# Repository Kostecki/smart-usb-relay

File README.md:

# Smart USB Relay

An inline USB-C box that switches and meters 5 V power to a USB gadget (lamp, fan, sensor) from Home Assistant. Charger → box → device.

- ESP32-H2 SuperMini running ESPHome over Thread (OTA, no Wi-Fi)
- TPS2557 current-limited switch (3 A), INA226 voltage/current/power metering → kWh in the Energy dashboard
- USB-C in and out: fixed 5 V sink towards the charger, 1.5 A / 3 A source towards the device (follows what the charger offers)
- 60 × 30 mm, 2 layers, assembled by JLCPCB (except the SuperMini, which sits on headers)

The full design, every decision behind it, and the pre-order checklist are in [SPEC.md](SPEC.md).

## Layout

| Path | What |
|---|---|
| `hardware/` | KiCad 10 project, project symbol/footprint libraries, footprints converted from LCSC (`lcsc/`) |
| `firmware/` | ESPHome configuration |
| `scripts/fab.sh` | ERC + DRC (with schematic parity), then Gerbers, drill, BOM and CPL for JLCPCB into `fab/` |

## Firmware

The config lives in the Home Assistant ESPHome dashboard (ESPHome 2026.10.0 or newer) and is edited there. `firmware/smart-usb-relay.yaml` is a copy, updated by hand when the behaviour changes.

1. In the dashboard's **Secrets**, add `thread_tlv` and `api_encryption_key` (`openssl rand -base64 32`; it also encrypts OTA). `firmware/secrets.example.yaml` explains how to get the Thread TLV with an Apple border router: send the credentials from the iPhone companion app, then read them with `thread/get_dataset_tlv` in the browser console.
2. Create a new device, skip the Wi-Fi questions, and replace its YAML with `firmware/smart-usb-relay.yaml`. For a second box, change `name` and `friendly_name` under `esphome:`.
3. Flash the SuperMini over its own USB-C **before** fitting it to the board: **Install → Plug into this computer** (Chrome or Edge). If the port doesn't show up, hold BOOT while plugging it in.
4. It joins your Thread network as a router and Home Assistant discovers it. Later updates: **Install → Wirelessly**.

Before it's on the board, the ADC pins float, so "Device attached" and the charger readings are meaningless.

Entities: Output, Device attached, Output powered, Overcurrent tripped, Voltage, Current, Power, Energy, Charger voltage, Charger advertised current, Advertised to device; config: Power-on behavior, Force output, Current limit.

## Order files

CI runs `scripts/fab.sh` on every change to the hardware and uploads `fab/` as a build artifact. Locally:

```sh
KICAD_CLI=/Applications/KiCad/KiCad.app/Contents/MacOS/kicad-cli scripts/fab.sh
```

Upload `fab/smart-usb-relay-gerbers.zip`, then the BOM and CPL for assembly. Leave U1 (SuperMini), the test pads and the mounting holes out of assembly (they're already excluded from the BOM and CPL), and choose "Remove Order Number".

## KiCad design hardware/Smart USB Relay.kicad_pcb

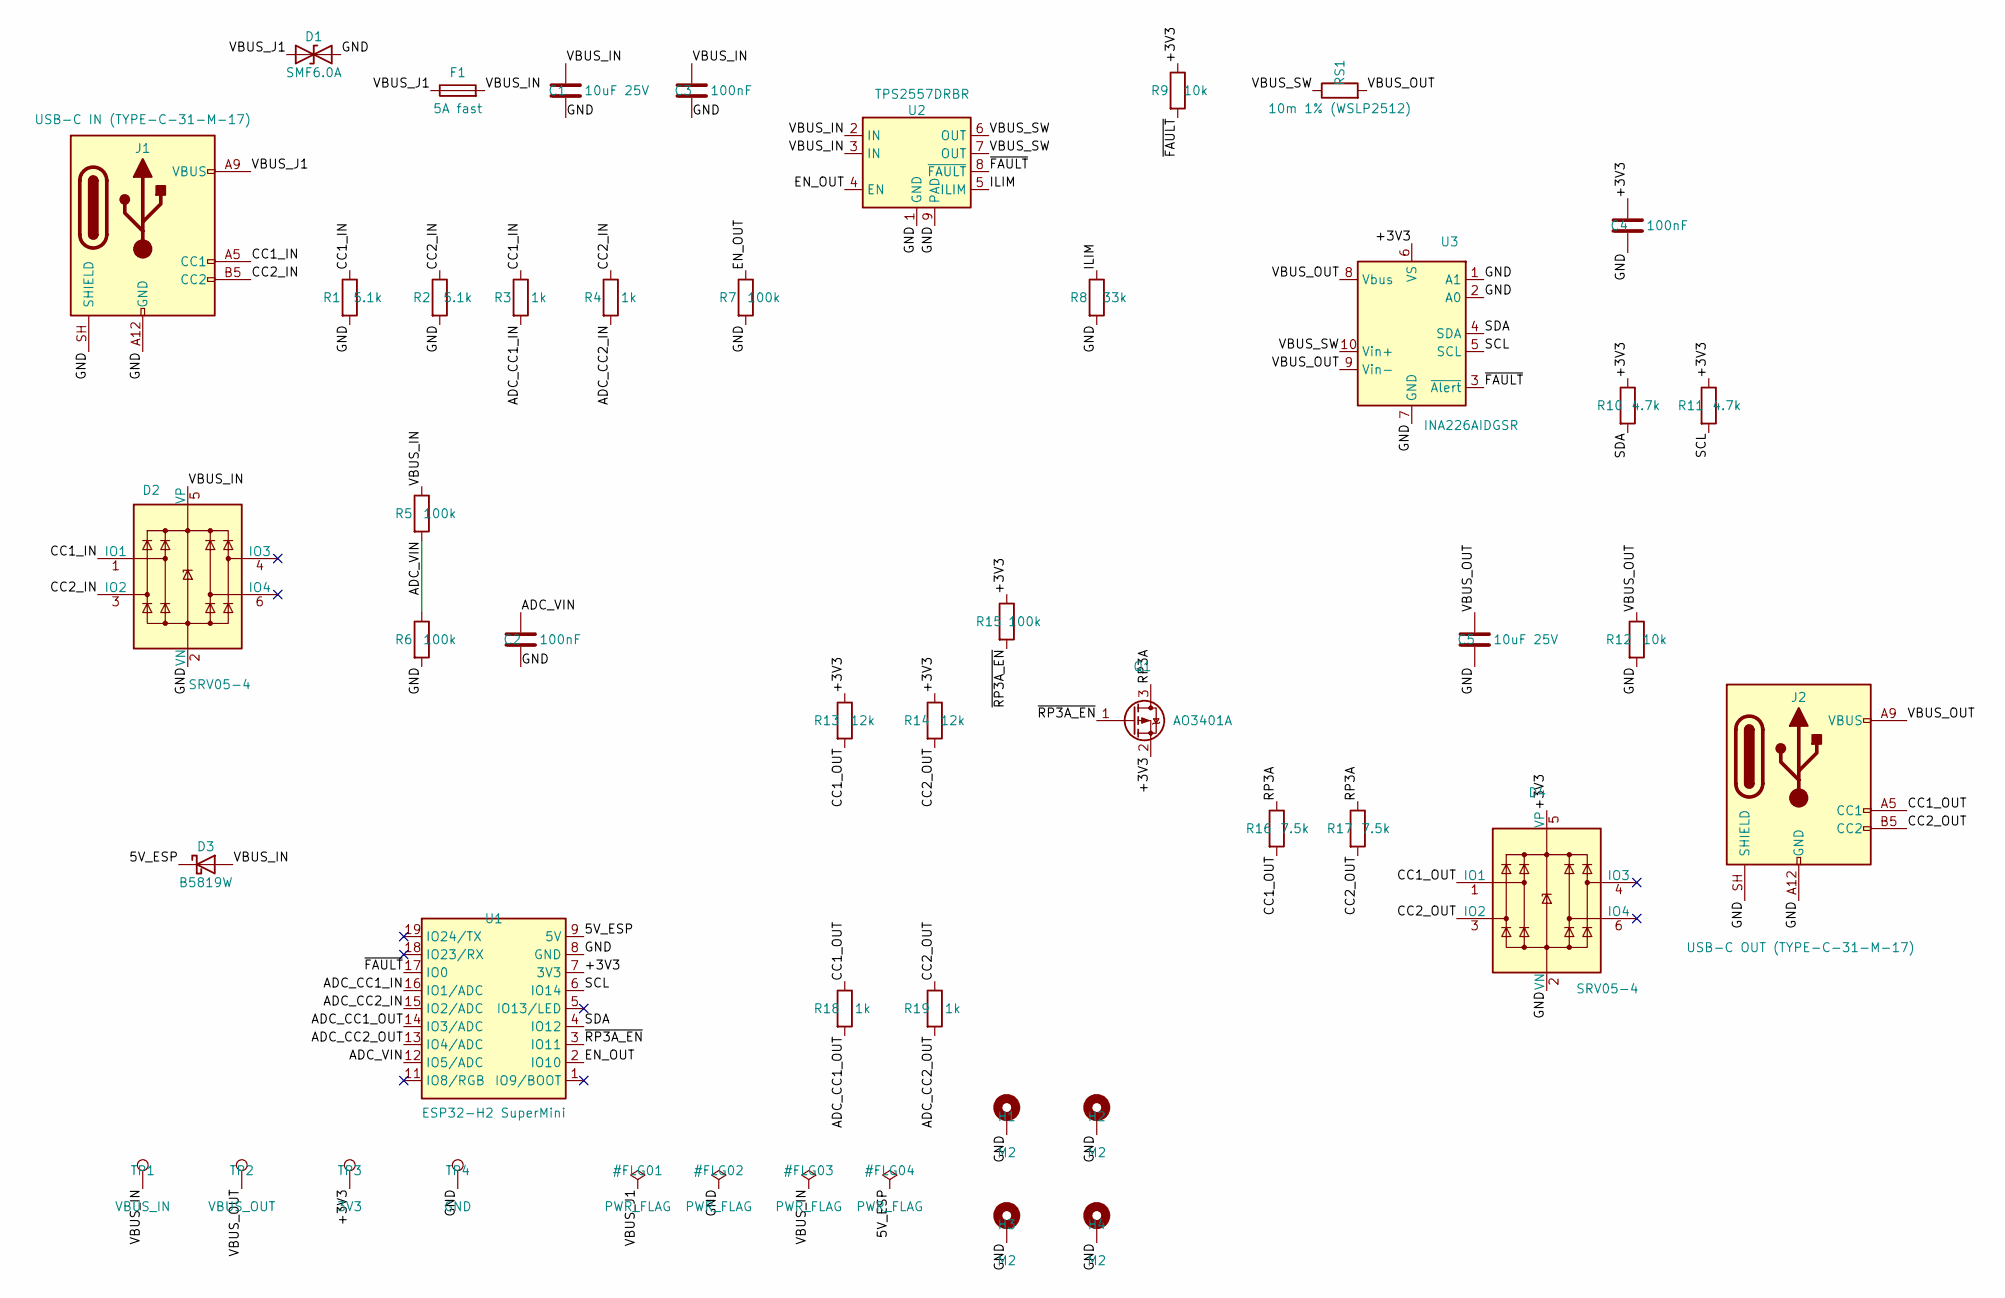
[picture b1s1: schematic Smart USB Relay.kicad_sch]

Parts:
C1, C5: 10uF 25V; C_0805_2012Metric; LCSC C15850
C2, C3, C4: 100nF; C_0603_1608Metric; LCSC C14663
D1: SMF6.0A; SOD-123FL_L2.7-W1.8-LS3.8-RD; LCSC C19077499
D2, D4: SRV05-4; SOT-23-6_L2.9-W1.6-P0.95-LS2.8-BR; LCSC C85364
D3: B5819W; SOD-123_L2.7-W1.6-LS3.7-RD-1; LCSC C8598
F1: 5A fast; F1206; LCSC C136351
H1, H2, H3, H4: M2; MountingHole_2.2mm_M2_Pad_Via
J1: USB-C IN (TYPE-C-31-M-17); USB_C_Receptacle_HRO_TYPE-C-31-M-17; LCSC C283540
J2: USB-C OUT (TYPE-C-31-M-17); USB_C_Receptacle_HRO_TYPE-C-31-M-17; LCSC C283540
Q1: AO3401A; SOT-23_L2.9-W1.3-P1.90-LS2.4-BR; LCSC C15127
R1, R2: 5.1k; R_0603_1608Metric; LCSC C23186
R3, R4, R18, R19: 1k; R_0603_1608Metric; LCSC C21190
R5, R6, R7, R15: 100k; R_0603_1608Metric; LCSC C25803
R8: 33k; R_0603_1608Metric; LCSC C4216
R9, R12: 10k; R_0603_1608Metric; LCSC C25804
R10, R11: 4.7k; R_0603_1608Metric; LCSC C23162
R13, R14: 12k; R_0603_1608Metric; LCSC C22790
R16, R17: 7.5k; R_0603_1608Metric; LCSC C23234
RS1: 10m 1% (WSLP2512); R2512; LCSC C241862
TP1: VBUS_IN; TestPoint_Pad_D1.5mm
TP2: VBUS_OUT; TestPoint_Pad_D1.5mm
TP3: 3V3; TestPoint_Pad_D1.5mm
TP4: GND; TestPoint_Pad_D1.5mm
U1: ESP32-H2 SuperMini; ESP32-H2_SuperMini_Header
U2: TPS2557DRBR; SON-8_L3.0-W3.0-P0.65-LS3.0-BL-EP; LCSC C130056
U3: INA226AIDGSR; MSOP-10_L3.0-W3.0-P0.50-LS5.0-BL; LCSC C49851

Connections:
/5V_ESP: D3.1 (K), U1.9 (5V)
/+3V3: C4.1, D4.5 (VP), Q1.2 (S), R9.1, R10.1, R11.1, R13.1, R14.1, R15.1, TP3.1, U1.7 (3V3), U3.6 (VS)
/ADC_CC1_IN: R3.2, U1.16 (IO1/ADC)
/ADC_CC1_OUT: R18.2, U1.14 (IO3/ADC)
/ADC_CC2_IN: R4.2, U1.15 (IO2/ADC)
/ADC_CC2_OUT: R19.2, U1.13 (IO4/ADC)
/ADC_VIN: C2.1, R5.2, R6.1, U1.12 (IO5/ADC)
/CC1_IN: D2.1 (IO1), J1.A5 (CC1), R1.1, R3.1
/CC1_OUT: D4.1 (IO1), J2.A5 (CC1), R13.2, R16.2, R18.1
/CC2_IN: D2.3 (IO2), J1.B5 (CC2), R2.1, R4.1
/CC2_OUT: D4.3 (IO2), J2.B5 (CC2), R14.2, R17.2, R19.1
/EN_OUT: R7.1, U1.2 (IO10), U2.4 (EN)
/GND: C1.2, C2.2, C3.2, C4.2, C5.2, D1.2 (A2), D2.2 (VN), D4.2 (VN), H1.1, H2.1, H3.1, H4.1, J1.A12 (GND), J1.B12 (GND), J1.SH (SHIELD), J2.A12 (GND), J2.B12 (GND), J2.SH (SHIELD), R1.2, R2.2, R6.2, R7.2, R8.2, R12.2, TP4.1, U1.8 (GND), U2.1 (GND), U2.9 (PAD), U3.1 (A1), U3.2 (A0), U3.7 (GND)
/ILIM: R8.1, U2.5 (ILIM)
/RP3A: Q1.3 (D), R16.1, R17.1
/SCL: R11.2, U1.6 (IO14), U3.5 (SCL)
/SDA: R10.2, U1.4 (IO12), U3.4 (SDA)
/VBUS_IN: C1.1, C3.1, D2.5 (VP), D3.2 (A), F1.2, R5.1, TP1.1, U2.2 (IN), U2.3 (IN)
/VBUS_J1: D1.1 (A1), F1.1, J1.A9 (VBUS), J1.B9 (VBUS)
/VBUS_OUT: C5.1, J2.A9 (VBUS), J2.B9 (VBUS), R12.1, RS1.2, TP2.1, U3.8 (Vbus), U3.9 (Vin-)
/VBUS_SW: RS1.1, U2.6 (OUT), U2.7 (OUT), U3.10 (Vin+)
/~FAULT: R9.2, U1.17 (IO0), U2.8 (~FAULT), U3.3 (~Alert)
/~RP3A_EN: Q1.1 (G), R15.2, U1.3 (IO11)

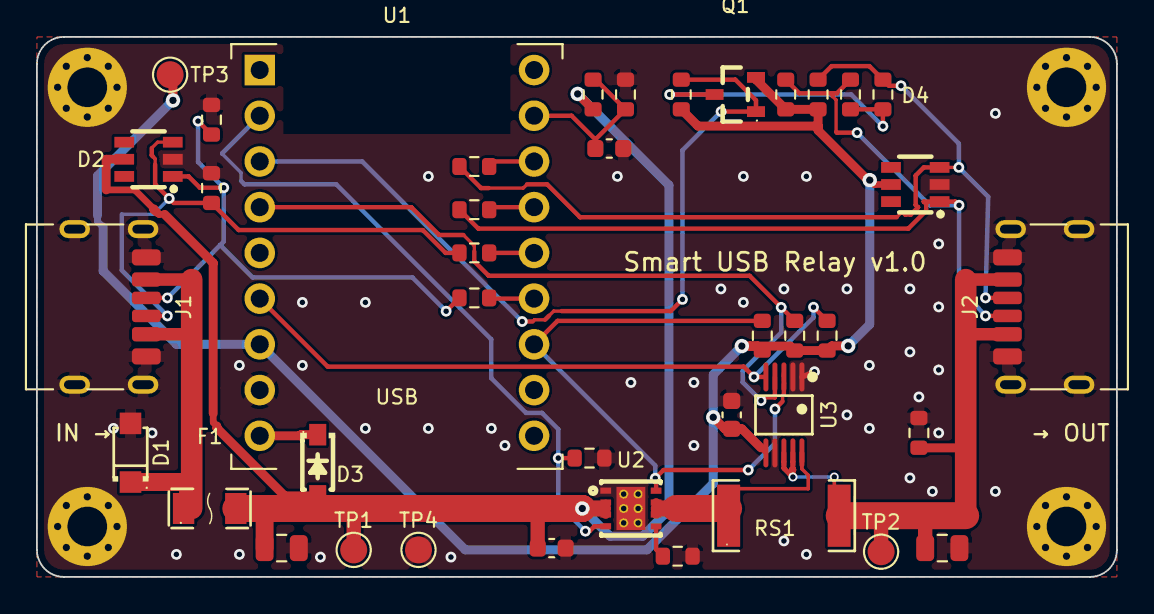
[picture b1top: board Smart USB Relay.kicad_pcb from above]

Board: 2 copper layers, 60.0 x 30.0 mm, 44 parts (0 on the bottom side), 23 nets.

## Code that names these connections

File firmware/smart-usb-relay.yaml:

# Board: Generic ESP32-H2 Board (Generic)
# Definition: definitions/boards/generic-esp32h2/manifest.yaml

# Smart USB Relay — ESP32-H2 SuperMini, ESPHome over Thread.
# Hardware, pin map and behaviour: ../SPEC.md
esphome:
  name: smart-usb-relay # unique per box
  friendly_name: Smart USB Relay
  min_version: 2026.10.0
  on_boot:
    # After the restored select/globals are loaded, apply the power-on behaviour.
    priority: -100
    then:
      - lambda: |-
          const auto option = id(power_on_behavior).current_option();
          if (option == "Off") {
            id(output_requested) = false;
          } else if (option == "On") {
            id(output_requested) = true;
          }
          // "Previous": keep the restored output_requested.

esp32:
  variant: esp32h2
  flash_size: 4MB # SuperMini: ESP32-H2 with 4 MB in-package flash
  framework:
    type: esp-idf

logger:
  level: INFO

network:
  enable_ipv6: true

openthread:
  device_type: FTD # mains powered, so a Thread router
  tlv: !secret thread_tlv
  force_dataset: true

api:
  encryption:
    key: !secret smart_usb_relay__api_encryption_key
ota:
  - platform: esphome
    encryption: {} # reuses the api encryption key

status_led:
  pin: GPIO13 # onboard blue LED, inside the case

i2c:
  sda: GPIO12
  scl: GPIO14
  frequency: 400kHz

globals:
  - id: output_requested # what the Output switch asks for (restored for "Previous")
    type: bool
    restore_value: true
    initial_value: "false"
  - id: overcurrent_latched
    type: bool
    initial_value: "false"
  - id: device_attached
    type: bool
    initial_value: "false"
  - id: overcurrent_samples # consecutive INA226 samples above the limit
    type: int
    initial_value: "0"

script:
  - id: trip_overcurrent
    then:
      - lambda: |-
          id(overcurrent_latched) = true;
          id(output_requested) = false;
          id(output_enable).turn_off();
          ESP_LOGW("relay", "Overcurrent: output latched off");

sensor:
  - platform: ina226
    address: 0x40
    shunt_resistance: 0.01 ohm
    max_current: 3.5A
    adc_averaging: 16
    update_interval: 200ms # fast for the software current limit; HA gets 10 s averages
    current:
      name: Current
      id: output_current
      accuracy_decimals: 3
      filters:
        - throttle_average: 10s
      on_raw_value:
        - lambda: |-
            if (id(output_enable).state && x > id(current_limit).state) {
              if (++id(overcurrent_samples) >= 2) {
                id(overcurrent_samples) = 0;
                id(trip_overcurrent).execute();
              }
            } else {
              id(overcurrent_samples) = 0;
            }
    power:
      name: Power
      id: output_power
      accuracy_decimals: 2
      filters:
        - throttle_average: 10s
    bus_voltage:
      name: Voltage
      accuracy_decimals: 2
      filters:
        - throttle_average: 10s

  - platform: integration
    name: Energy
    sensor: output_power
    time_unit: h
    unit_of_measurement: kWh
    device_class: energy
    state_class: total_increasing
    accuracy_decimals: 4
    restore: true
    filters:
      - multiply: 0.001

  # USB-C CC lines and charger voltage, read through 1 kΩ series resistors.
  - platform: adc
    id: cc1_in
    pin: GPIO1
    attenuation: 12db
    update_interval: 100ms
    internal: true
  - platform: adc
    id: cc2_in
    pin: GPIO2
    attenuation: 12db
    update_interval: 100ms
    internal: true
  - platform: adc
    id: cc1_out
    pin: GPIO3
    attenuation: 12db
    update_interval: 100ms
    internal: true
  - platform: adc
    id: cc2_out
    pin: GPIO4
    attenuation: 12db
    update_interval: 100ms
    internal: true
  - platform: adc
    name: Charger voltage
    pin: GPIO5
    attenuation: 12db
    update_interval: 1s
    accuracy_decimals: 2
    entity_category: diagnostic
    filters:
      - multiply: 2.0 # 100k/100k divider
      - throttle_average: 10s

binary_sensor:
  - platform: gpio
    id: hw_fault # TPS2557 FAULT and INA226 ALERT, open drain, 10 kΩ pull-up
    pin:
      number: GPIO0
      inverted: true
    internal: true
    filters:
      - delayed_on: 20ms # on top of the TPS2557's own 6-13 ms deglitch
    on_press:
      - script.execute: trip_overcurrent
  - platform: template
    name: Device attached
    lambda: return id(device_attached);
  - platform: template
    name: Output powered
    device_class: power
    lambda: return id(output_enable).state;
  - platform: template
    name: Overcurrent tripped
    device_class: problem
    lambda: return id(overcurrent_latched);

text_sensor:
  - platform: template
    id: charger_current
    name: Charger advertised current
    entity_category: diagnostic
    update_interval: never
  - platform: template
    id: device_current
    name: Advertised to device
    entity_category: diagnostic
    update_interval: never

switch:
  - platform: gpio
    id: output_enable # TPS2557 EN, 100 kΩ pull-down keeps it off during boot
    pin: GPIO10
    internal: true
    restore_mode: ALWAYS_OFF
  - platform: gpio
    id: rp_3a # Q1 gate, active low: adds the 3 A Rp on CC_OUT
    pin:
      number: GPIO11
      inverted: true
    internal: true
    restore_mode: ALWAYS_OFF
  - platform: template
    name: Output
    id: output_switch
    icon: mdi:power-socket-eu
    lambda: return id(output_requested);
    turn_on_action:
      - lambda: |-
          id(overcurrent_latched) = false;
          id(output_requested) = true;
    turn_off_action:
      - lambda: id(output_requested) = false;
  - platform: template
    name: Force output
    id: force_output # for cables without Rd (bare USB-C to barrel/wire)
    icon: mdi:power-plug-outline
    entity_category: config
    optimistic: true
    restore_mode: RESTORE_DEFAULT_OFF

select:
  - platform: template
    name: Power-on behavior
    id: power_on_behavior
    entity_category: config
    options: ["Off", "On", "Previous"]
    initial_option: "Off"
    optimistic: true
    restore_value: true

number:
  - platform: template
    name: Current limit
    id: current_limit
    entity_category: config
    unit_of_measurement: A
    min_value: 0.5
    max_value: 3.5
    step: 0.1
    initial_value: 3.0
    optimistic: true
    restore_value: true
    mode: box

button:
  - platform: restart
    name: Restart
    entity_category: config

interval:
  - interval: 100ms
    then:
      - lambda: |-
          // Charger side: our 5.1 kΩ Rd against the charger's Rp (USB Type-C vRd thresholds).
          const float cc_in = std::max(id(cc1_in).state, id(cc2_in).state);
          const char *charger = cc_in >= 1.23f ? "3 A" : cc_in >= 0.66f ? "1.5 A" : cc_in >= 0.2f ? "Default" : "Unknown";
          if (id(charger_current).state != charger) id(charger_current).publish_state(charger);

          // Advertise 3 A to the device only when the charger offers 3 A.
          const bool want_3a = cc_in >= 1.23f;
          if (id(rp_3a).state != want_3a) {
            if (want_3a) id(rp_3a).turn_on(); else id(rp_3a).turn_off();
          }
          const char *advertised = want_3a ? "3 A" : "1.5 A";
          if (id(device_current).state != advertised) id(device_current).publish_state(advertised);

          // Device side: our Rp to 3V3 against the device's 5.1 kΩ Rd. Below the window is
          // Ra (e-marked cable) or nothing; above it the line is open (pulled up to 3V3).
          const float lo = id(rp_3a).state ? 0.80f : 0.40f;
          const float hi = id(rp_3a).state ? 2.60f : 1.60f;
          auto is_rd = [&](float v) { return v >= lo && v <= hi; };
          const bool rd_now = is_rd(id(cc1_out).state) || is_rd(id(cc2_out).state);
          // Attach after 2 consecutive reads (~200 ms debounce), detach immediately.
          static int attach_reads = 0;
          attach_reads = rd_now ? std::min(attach_reads + 1, 2) : 0;
          id(device_attached) = attach_reads >= 2;

          const bool power = id(output_requested) && !id(overcurrent_latched) &&
                             (id(device_attached) || id(force_output).state);
          if (power != id(output_enable).state) {
            if (power) id(output_enable).turn_on(); else id(output_enable).turn_off();
          }
